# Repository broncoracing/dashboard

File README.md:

# template
Use this repo as the base for new repos.
Follow directory structure below:

```bash
├── firmware
│   └── firmware project
└── pcb
    ├── PCB layout
    ├── schematic
    └── etc
```

Upon pushing a commit, a Github action will automatically run electrical & design rule checks to verify the pcb design, then generate gerber/drill/BOM files and renderings/PDFs of the pcb and schematics.

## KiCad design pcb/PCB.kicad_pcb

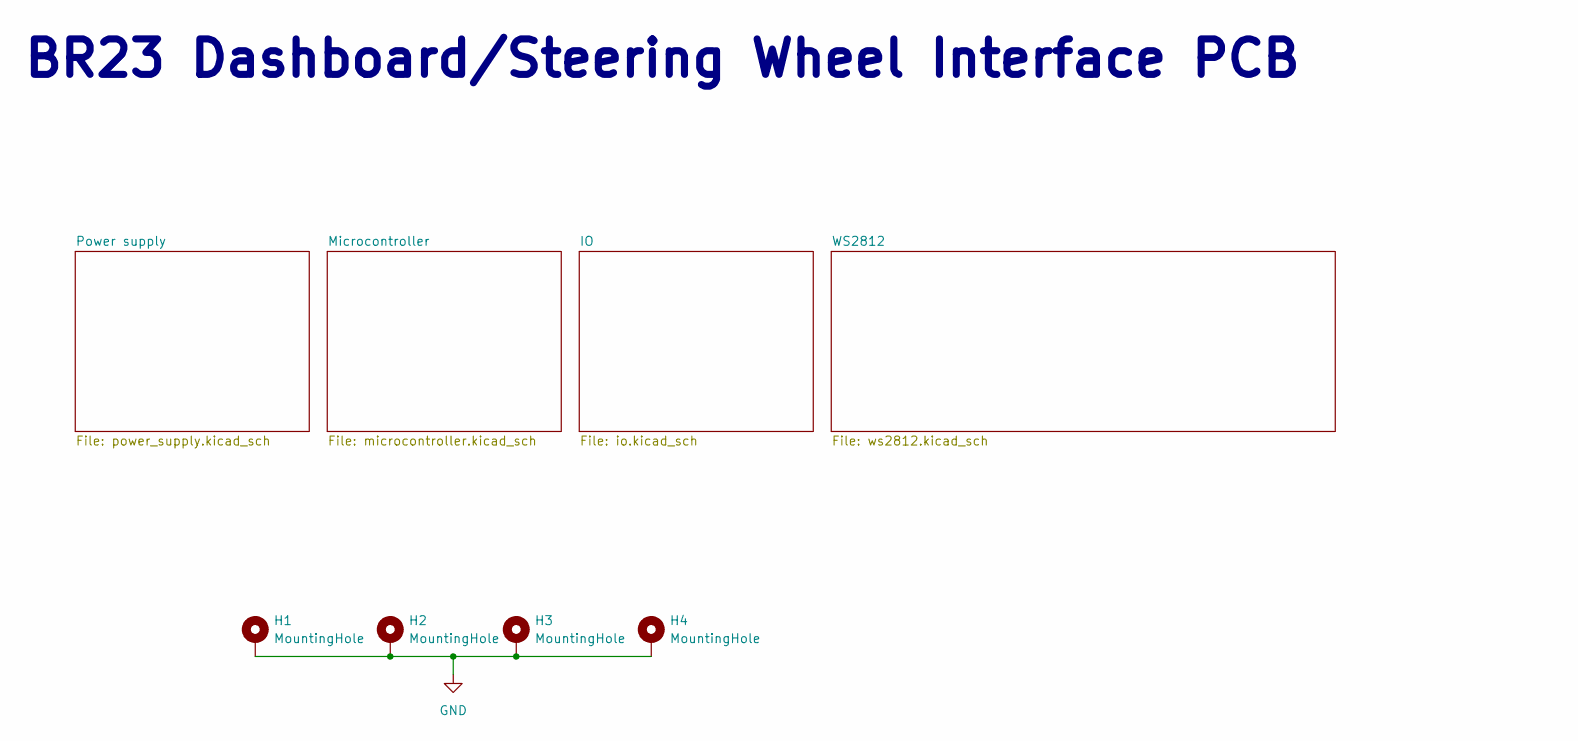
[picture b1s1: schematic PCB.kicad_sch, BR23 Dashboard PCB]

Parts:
H1, H2, H3, H4: MountingHole; MountingHole_3.5mm_Pad

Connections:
GND: H1.1, H2.1, H3.1, H4.1; also elsewhere on the board

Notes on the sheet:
BR23 Dashboard/Steering Wheel Interface PCB

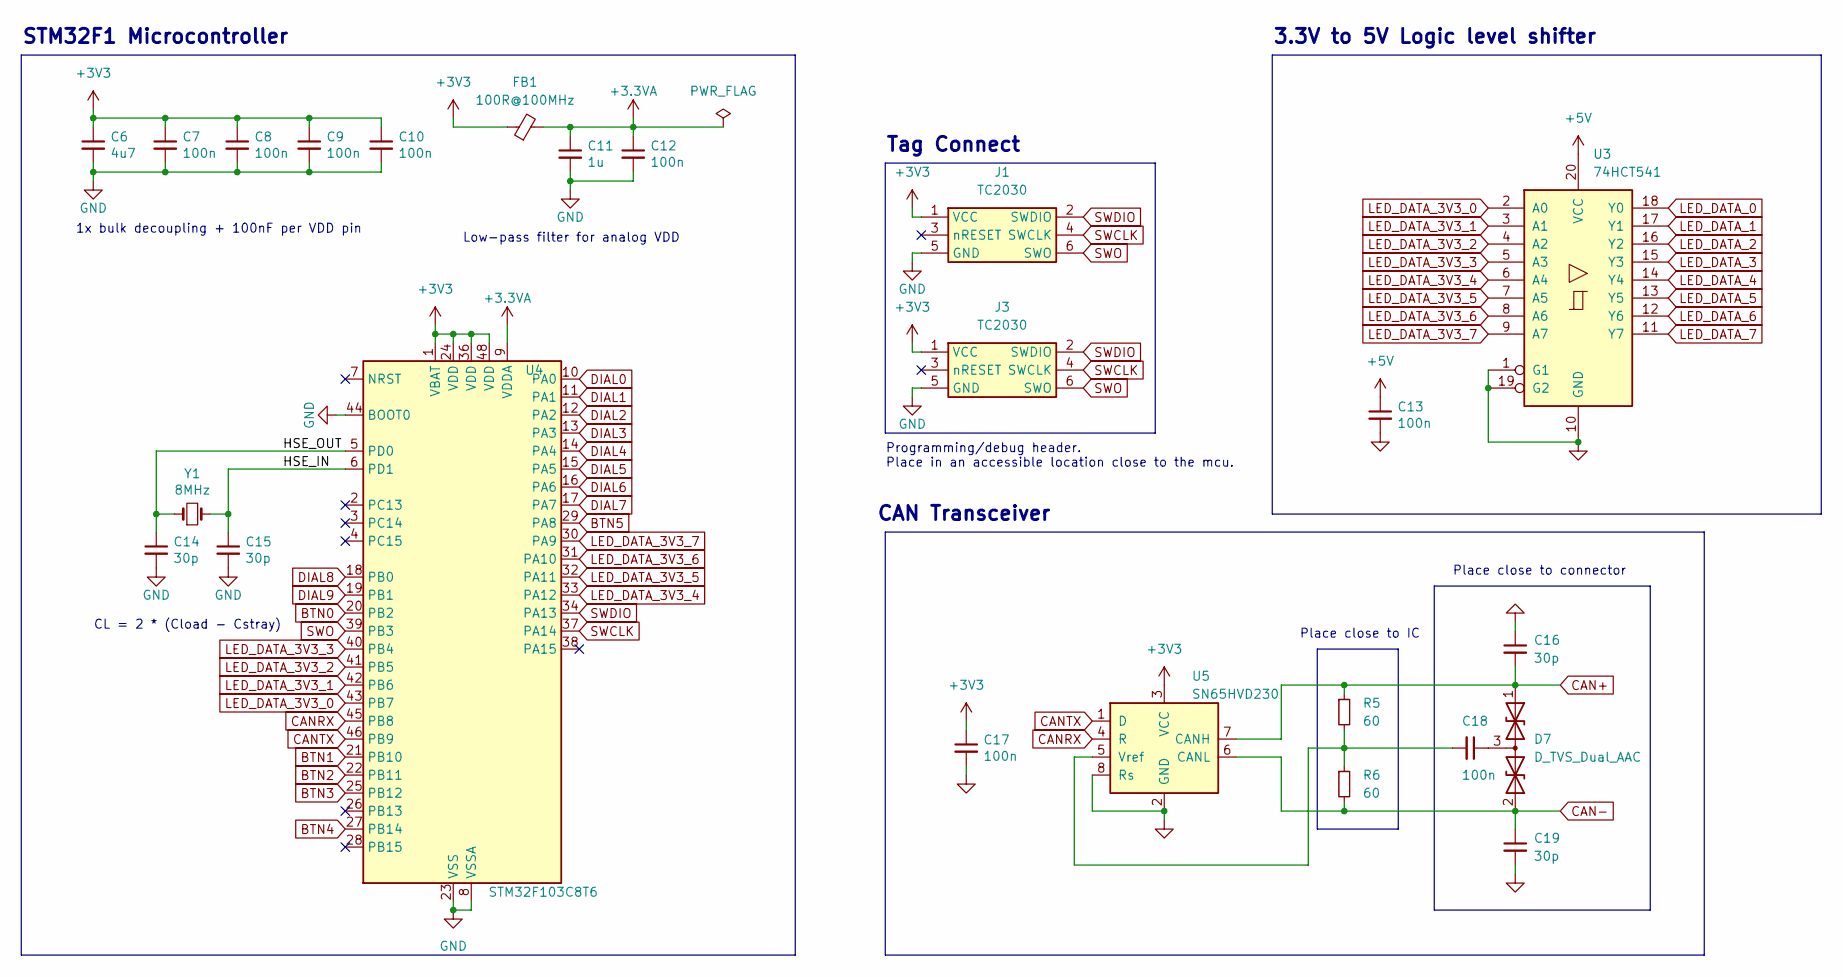
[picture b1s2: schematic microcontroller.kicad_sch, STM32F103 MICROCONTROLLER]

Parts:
C6: 4u7; C_0603_1608Metric; LCSC C19666
C7, C8, C9, C10, C12, C13, C17, C18: 100n; C_0402_1005Metric; LCSC C307331
C11: 1u; C_0603_1608Metric; LCSC C15849
C14, C15, C16, C19: 30p; C_0402_1005Metric; LCSC C1570
D7: D_TVS_Dual_AAC; SOT-323_SC-70; LCSC C151237
FB1: 100R@100MHz; R_0805_2012Metric; LCSC C1015
J1, J3: TC2030; Tag-Connect_TC2030-IDC-NL_2x03_P1.27mm_Vertical
R5, R6: 60; R_0805_2012Metric; LCSC C844855
U3: 74HCT541; SSOP-20_4.4x6.5mm_P0.65mm; LCSC C6758
U4: STM32F103C8T6; LQFP-48_7x7mm_P0.5mm; LCSC C77994
U5: SN65HVD230; SOIC-8_3.9x4.9mm_P1.27mm; LCSC C12084
Y1: 8MHz; Crystal_SMD_5032-2Pin_5.0x3.2mm; LCSC C115962

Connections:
+3.3VA: C11.1, C12.1, FB1.2, U4.9 (VDDA); also elsewhere on the board
+3V3: C6.1, C7.1, C8.1, C9.1, C10.1, C17.1, FB1.1, J1.1 (VCC), J3.1 (VCC), U4.1 (VBAT), U4.24 (VDD), U4.36 (VDD), U4.48 (VDD), U5.3 (VCC); also elsewhere on the board
+5V: C13.1, U3.20 (VCC); also elsewhere on the board
/Microcontroller/HSE_IN: C15.1, U4.6 (PD1), Y1.2
/Microcontroller/HSE_OUT: C14.1, U4.5 (PD0), Y1.1
BTN0: U4.20 (PB2); also elsewhere on the board
BTN1: U4.21 (PB10); also elsewhere on the board
BTN2: U4.22 (PB11); also elsewhere on the board
BTN3: U4.25 (PB12); also elsewhere on the board
BTN4: U4.27 (PB14); also elsewhere on the board
BTN5: U4.29 (PA8); also elsewhere on the board
CAN+: C16.2, D7.1 (A1), R5.1, U5.7 (CANH); also elsewhere on the board
CAN-: C19.1, D7.2 (A2), R6.2, U5.6 (CANL); also elsewhere on the board
CANRX: U4.45 (PB8), U5.4 (R)
CANTX: U4.46 (PB9), U5.1 (D)
DIAL0: U4.10 (PA0); also elsewhere on the board
DIAL1: U4.11 (PA1); also elsewhere on the board
DIAL2: U4.12 (PA2); also elsewhere on the board
DIAL3: U4.13 (PA3); also elsewhere on the board
DIAL4: U4.14 (PA4); also elsewhere on the board
DIAL5: U4.15 (PA5); also elsewhere on the board
DIAL6: U4.16 (PA6); also elsewhere on the board
DIAL7: U4.17 (PA7); also elsewhere on the board
DIAL8: U4.18 (PB0); also elsewhere on the board
DIAL9: U4.19 (PB1); also elsewhere on the board
GND: C6.2, C7.2, C8.2, C9.2, C10.2, C11.2, C12.2, C13.2, C14.2, C15.2, C16.1, C17.2, C19.2, J1.5 (GND), J3.5 (GND), U3.1 (G1), U3.10 (GND), U3.19 (G2), U4.8 (VSSA), U4.23 (VSS), U4.35 (VSS), U4.44 (BOOT0), U4.47 (VSS), U5.2 (GND), U5.8 (Rs); also elsewhere on the board
LED_DATA_0: U3.18 (Y0); also elsewhere on the board
LED_DATA_1: U3.17 (Y1); also elsewhere on the board
LED_DATA_2: U3.16 (Y2); also elsewhere on the board
LED_DATA_3: U3.15 (Y3); also elsewhere on the board
LED_DATA_3V3_0: U3.2 (A0), U4.43 (PB7)
LED_DATA_3V3_1: U3.3 (A1), U4.42 (PB6)
LED_DATA_3V3_2: U3.4 (A2), U4.41 (PB5)
LED_DATA_3V3_3: U3.5 (A3), U4.40 (PB4)
LED_DATA_3V3_4: U3.6 (A4), U4.33 (PA12)
LED_DATA_3V3_5: U3.7 (A5), U4.32 (PA11)
LED_DATA_3V3_6: U3.8 (A6), U4.31 (PA10)
LED_DATA_3V3_7: U3.9 (A7), U4.30 (PA9)
LED_DATA_4: U3.14 (Y4); also elsewhere on the board
LED_DATA_5: U3.13 (Y5); also elsewhere on the board
LED_DATA_6: U3.12 (Y6); also elsewhere on the board
LED_DATA_7: U3.11 (Y7); also elsewhere on the board
unnamed: C18.1, D7.3 (common)
unnamed: C18.2, R5.2, R6.1, U5.5 (Vref)
SWCLK: J1.4 (SWCLK), J3.4 (SWCLK), U4.37 (PA14)
SWDIO: J1.2 (SWDIO), J3.2 (SWDIO), U4.34 (PA13)
SWO: J1.6 (SWO), J3.6 (SWO), U4.39 (PB3)

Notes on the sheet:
3.3V to 5V Logic level shifter
Tag Connect
Low-pass filter for analog VDD
Programming/debug header. Place in an accessible location close to the mcu.
CAN Transceiver
Place close to connector
1x bulk decoupling + 100nF per VDD pin
STM32F1 Microcontroller
Place close to IC
CL = 2 * (Cload - Cstray)

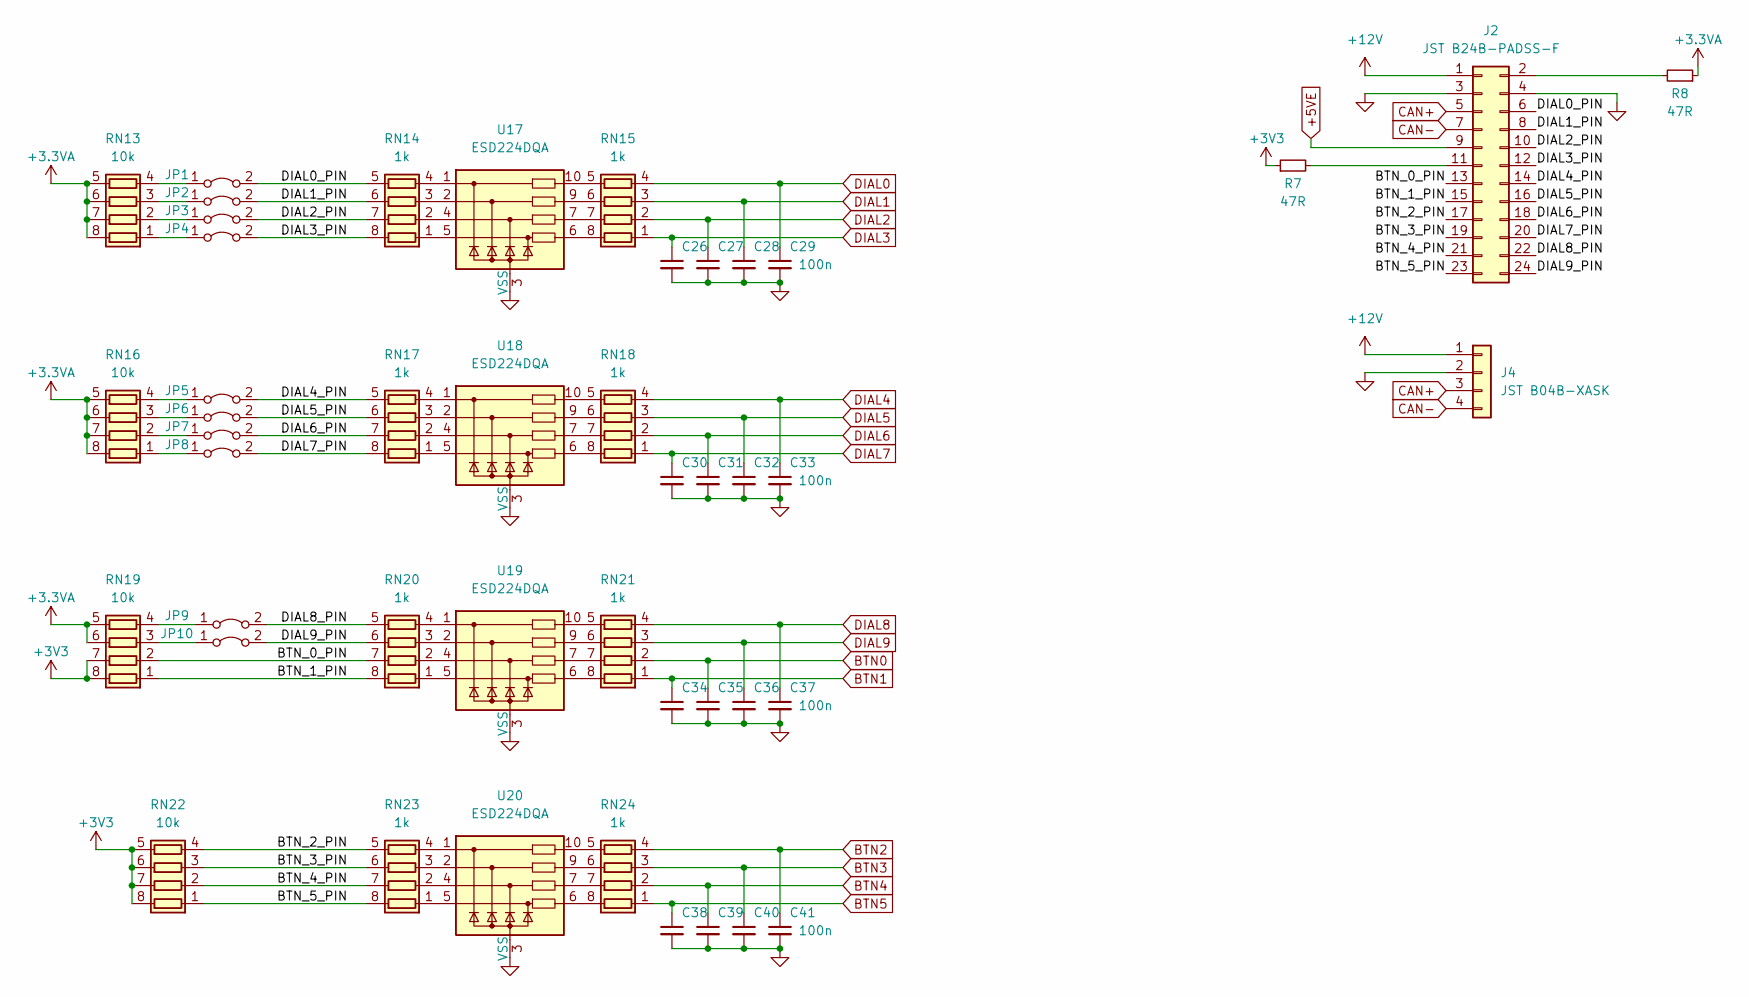
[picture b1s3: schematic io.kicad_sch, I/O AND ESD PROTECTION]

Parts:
C26, C27, C28, C29, C30, C31, C32, C33, C34, C35, C36, C37, C38, C39, C40, C41: 100n; C_0402_1005Metric; LCSC C307331
J2: JST B24B-PADSS-F; JST_B24B_PADSS; LCSC C5329907
J4: JST B04B-XASK; JST_XA_B04B-XASK-1_1x04_P2.50mm_Vertical; LCSC C160300
JP1, JP2, JP3, JP4, JP5, JP6, JP7, JP8, JP9, JP10: Jumper_2_Bridged; TestPoint_2Pads_Pitch2.54mm_Drill0.8mm
R7, R8: 47R; R_0805_2012Metric; LCSC C17714
RN13, RN16, RN19, RN22: 10k; R_Array_Convex_4x0603; LCSC C29718
RN14, RN15, RN17, RN18, RN20, RN21, RN23, RN24: 1k; R_Array_Convex_4x0603; LCSC C20197
U17, U18, U19, U20: ESD224DQA; Diodes_UDFN-10_1.0x2.5mm_P0.5mm; LCSC C1981316

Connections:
+3.3VA: R8.1, RN13.5 (R4.2), RN13.6 (R3.2), RN13.7 (R2.2), RN13.8 (R1.2), RN16.5 (R4.2), RN16.6 (R3.2), RN16.7 (R2.2), RN16.8 (R1.2), RN19.5 (R4.2), RN19.6 (R3.2); also elsewhere on the board
+3V3: R7.1, RN19.7 (R2.2), RN19.8 (R1.2), RN22.5 (R4.2), RN22.6 (R3.2), RN22.7 (R2.2), RN22.8 (R1.2); also elsewhere on the board
+5VE: J2.9; also elsewhere on the board
+12V: J2.1, J4.1; also elsewhere on the board
/IO/BTN_0_PIN: J2.13, RN19.2 (R2.1), RN20.7 (R2.2)
/IO/BTN_1_PIN: J2.15, RN19.1 (R1.1), RN20.8 (R1.2)
/IO/BTN_2_PIN: J2.17, RN22.4 (R4.1), RN23.5 (R4.2)
/IO/BTN_3_PIN: J2.19, RN22.3 (R3.1), RN23.6 (R3.2)
/IO/BTN_4_PIN: J2.21, RN22.2 (R2.1), RN23.7 (R2.2)
/IO/BTN_5_PIN: J2.23, RN22.1 (R1.1), RN23.8 (R1.2)
/IO/DIAL0_PIN: J2.6, JP1.2 (B), RN14.5 (R4.2)
/IO/DIAL1_PIN: J2.8, JP2.2 (B), RN14.6 (R3.2)
/IO/DIAL2_PIN: J2.10, JP3.2 (B), RN14.7 (R2.2)
/IO/DIAL3_PIN: J2.12, JP4.2 (B), RN14.8 (R1.2)
/IO/DIAL4_PIN: J2.14, JP5.2 (B), RN17.5 (R4.2)
/IO/DIAL5_PIN: J2.16, JP6.2 (B), RN17.6 (R3.2)
/IO/DIAL6_PIN: J2.18, JP7.2 (B), RN17.7 (R2.2)
/IO/DIAL7_PIN: J2.20, JP8.2 (B), RN17.8 (R1.2)
/IO/DIAL8_PIN: J2.22, JP9.2 (B), RN20.5 (R4.2)
/IO/DIAL9_PIN: J2.24, JP10.2 (B), RN20.6 (R3.2)
BTN0: C35.1, RN21.2 (R2.1); also elsewhere on the board
BTN1: C34.1, RN21.1 (R1.1); also elsewhere on the board
BTN2: C41.1, RN24.4 (R4.1); also elsewhere on the board
BTN3: C40.1, RN24.3 (R3.1); also elsewhere on the board
BTN4: C39.1, RN24.2 (R2.1); also elsewhere on the board
BTN5: C38.1, RN24.1 (R1.1); also elsewhere on the board
CAN+: J2.5, J4.3; also elsewhere on the board
CAN-: J2.7, J4.4; also elsewhere on the board
DIAL0: C29.1, RN15.4 (R4.1); also elsewhere on the board
DIAL1: C28.1, RN15.3 (R3.1); also elsewhere on the board
DIAL2: C27.1, RN15.2 (R2.1); also elsewhere on the board
DIAL3: C26.1, RN15.1 (R1.1); also elsewhere on the board
DIAL4: C33.1, RN18.4 (R4.1); also elsewhere on the board
DIAL5: C32.1, RN18.3 (R3.1); also elsewhere on the board
DIAL6: C31.1, RN18.2 (R2.1); also elsewhere on the board
DIAL7: C30.1, RN18.1 (R1.1); also elsewhere on the board
DIAL8: C37.1, RN21.4 (R4.1); also elsewhere on the board
DIAL9: C36.1, RN21.3 (R3.1); also elsewhere on the board
GND: C26.2, C27.2, C28.2, C29.2, C30.2, C31.2, C32.2, C33.2, C34.2, C35.2, C36.2, C37.2, C38.2, C39.2, C40.2, C41.2, J2.3, J2.4, J4.2, U17.3 (VSS), U17.8 (VSS), U18.3 (VSS), U18.8 (VSS), U19.3 (VSS), U19.8 (VSS), U20.3 (VSS), U20.8 (VSS); also elsewhere on the board
unnamed: J2.2, R8.2
unnamed: J2.11, R7.2
unnamed: JP1.1 (A), RN13.4 (R4.1)
unnamed: JP2.1 (A), RN13.3 (R3.1)
unnamed: JP3.1 (A), RN13.2 (R2.1)
unnamed: JP4.1 (A), RN13.1 (R1.1)
unnamed: JP5.1 (A), RN16.4 (R4.1)
unnamed: JP6.1 (A), RN16.3 (R3.1)
unnamed: JP7.1 (A), RN16.2 (R2.1)
unnamed: JP8.1 (A), RN16.1 (R1.1)
unnamed: JP9.1 (A), RN19.4 (R4.1)
unnamed: JP10.1 (A), RN19.3 (R3.1)
unnamed: RN14.1 (R1.1), U17.5
unnamed: RN14.2 (R2.1), U17.4
unnamed: RN14.3 (R3.1), U17.2
unnamed: RN14.4 (R4.1), U17.1
unnamed: RN15.8 (R1.2), U17.6
unnamed: RN15.7 (R2.2), U17.7
unnamed: RN15.6 (R3.2), U17.9
unnamed: RN15.5 (R4.2), U17.10
unnamed: RN17.1 (R1.1), U18.5
unnamed: RN17.2 (R2.1), U18.4
unnamed: RN17.3 (R3.1), U18.2
unnamed: RN17.4 (R4.1), U18.1
unnamed: RN18.8 (R1.2), U18.6
unnamed: RN18.7 (R2.2), U18.7
unnamed: RN18.6 (R3.2), U18.9
unnamed: RN18.5 (R4.2), U18.10
unnamed: RN20.1 (R1.1), U19.5
unnamed: RN20.2 (R2.1), U19.4
unnamed: RN20.3 (R3.1), U19.2
unnamed: RN20.4 (R4.1), U19.1
unnamed: RN21.8 (R1.2), U19.6
unnamed: RN21.7 (R2.2), U19.7
unnamed: RN21.6 (R3.2), U19.9
unnamed: RN21.5 (R4.2), U19.10
unnamed: RN23.1 (R1.1), U20.5
unnamed: RN23.2 (R2.1), U20.4
unnamed: RN23.3 (R3.1), U20.2
unnamed: RN23.4 (R4.1), U20.1
unnamed: RN24.8 (R1.2), U20.6
unnamed: RN24.7 (R2.2), U20.7
unnamed: RN24.6 (R3.2), U20.9
unnamed: RN24.5 (R4.2), U20.10

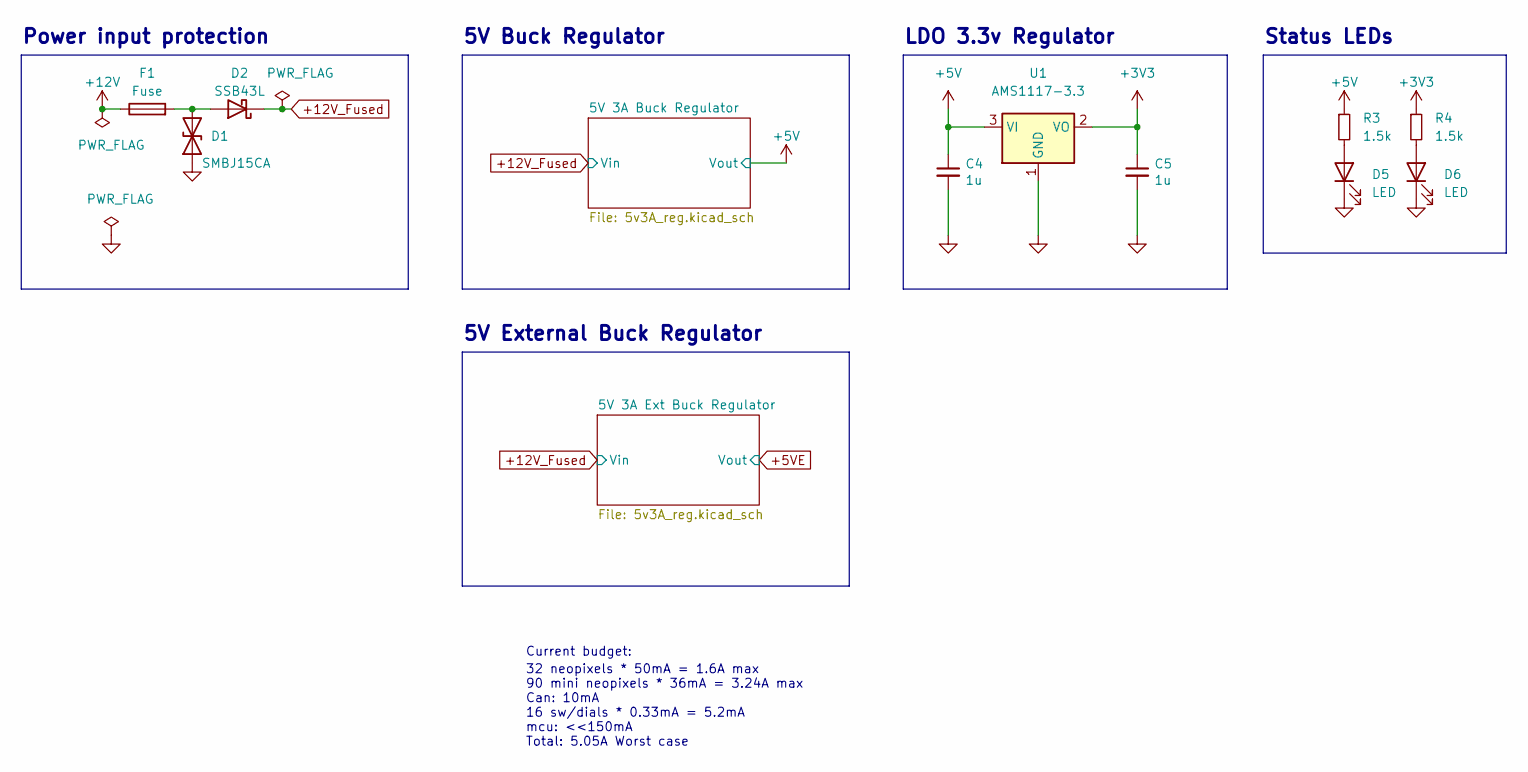
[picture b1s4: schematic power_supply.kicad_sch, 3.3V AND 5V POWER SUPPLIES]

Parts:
C4, C5: 1u; C_0603_1608Metric; LCSC C15849
D1: SMBJ15CA; D_SMB; LCSC C78809
D2: SSB43L; D_SMB; LCSC C222519
D5, D6: LED; LED_0603_1608Metric; LCSC C5875739
F1: Fuse; Fuse_0603_1608Metric; LCSC C122964
R3, R4: 1.5k; R_0603_1608Metric; LCSC C4177
U1: AMS1117-3.3; SOT-223-3_TabPin2; LCSC C6186

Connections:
+3V3: C5.1, R4.1, U1.2 (VO); also elsewhere on the board
+5V: C4.1, R3.1, U1.3 (VI); also elsewhere on the board
+12V: F1.1; also elsewhere on the board
+12V_Fused: D2.1 (K); also elsewhere on the board
GND: C4.2, C5.2, D1.1 (A1), D5.1 (K), D6.1 (K), U1.1 (GND); also elsewhere on the board
unnamed: D1.2 (A2), D2.2 (A), F1.2
unnamed: D5.2 (A), R3.2
unnamed: D6.2 (A), R4.2

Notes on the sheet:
5V External Buck Regulator
Power input protection
5V Buck Regulator
Current budget:
Status LEDs
LDO 3.3v Regulator
32 neopixels * 50mA = 1.6A max 90 mini neopixels * 36mA = 3.24A max Can: 10mA 16 sw/dials * 0.33mA = 5.2mA mcu: <<150mA Total: 5.05A Worst case

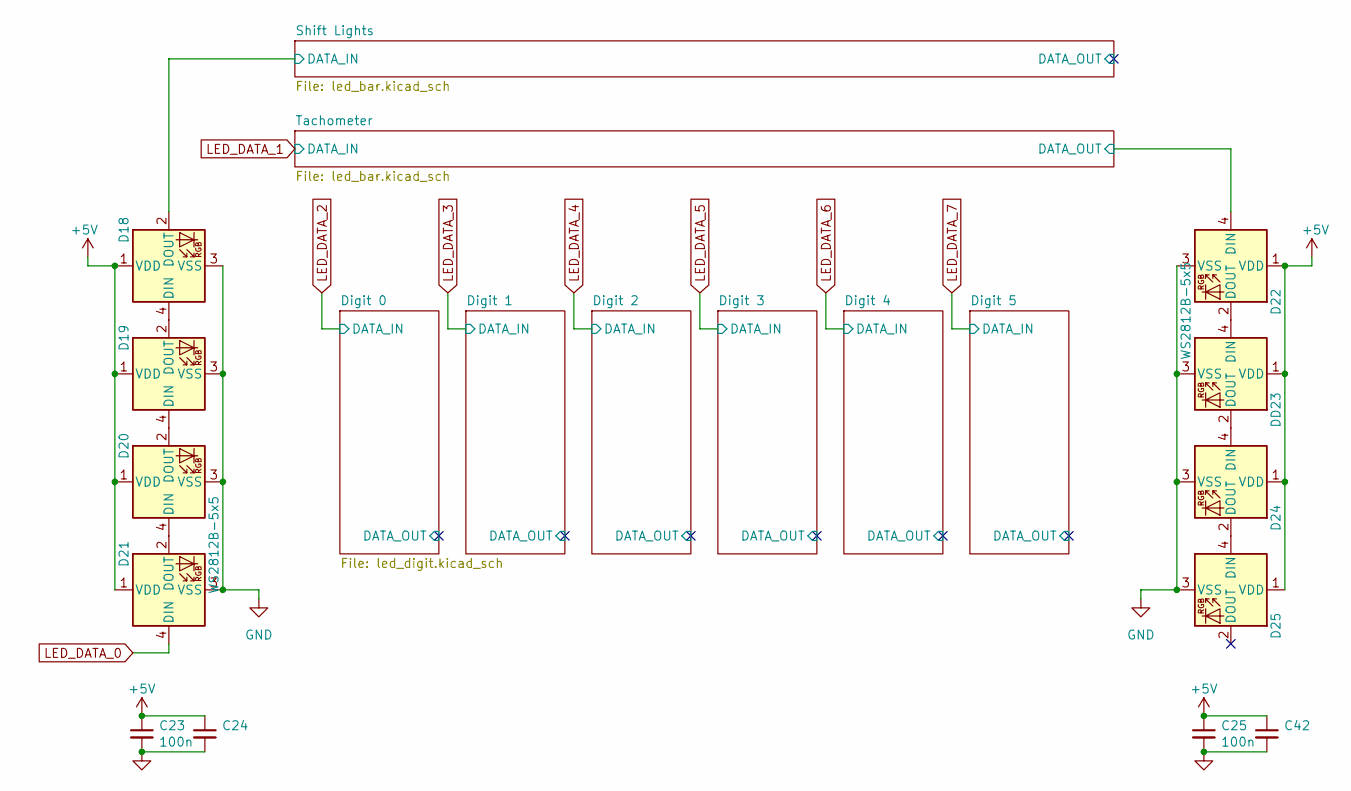
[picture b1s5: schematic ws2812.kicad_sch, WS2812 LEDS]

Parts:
C23, C24, C25, C42: 100n; C_0402_1005Metric; LCSC C307331
D18, D19, D20, D21, D22, D24, D25: WS2812B-5x5; LED_WS2812B_PLCC4_5.0x5.0mm_P3.2mm; LCSC C22371521
DD23: WS2812B-5x5; LED_WS2812B_PLCC4_5.0x5.0mm_P3.2mm; LCSC C22371521

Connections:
+5V: C23.1, C24.1, C25.1, C42.1, D18.1 (VDD), D19.1 (VDD), D20.1 (VDD), D21.1 (VDD), D22.1 (VDD), D24.1 (VDD), D25.1 (VDD), DD23.1 (VDD); also elsewhere on the board
/WS2812/Shift Lights/DATA_IN: D18.2 (DOUT); also elsewhere on the board
/WS2812/Tachometer/DATA_OUT: D22.4 (DIN); also elsewhere on the board
GND: C23.2, C24.2, C25.2, C42.2, D18.3 (VSS), D19.3 (VSS), D20.3 (VSS), D21.3 (VSS), D22.3 (VSS), D24.3 (VSS), D25.3 (VSS), DD23.3 (VSS); also elsewhere on the board
LED_DATA_0: D21.4 (DIN); also elsewhere on the board
unnamed: D18.4 (DIN), D19.2 (DOUT)
unnamed: D19.4 (DIN), D20.2 (DOUT)
unnamed: D20.4 (DIN), D21.2 (DOUT)
unnamed: D22.2 (DOUT), DD23.4 (DIN)
unnamed: D24.4 (DIN), DD23.2 (DOUT)
unnamed: D24.2 (DOUT), D25.4 (DIN)

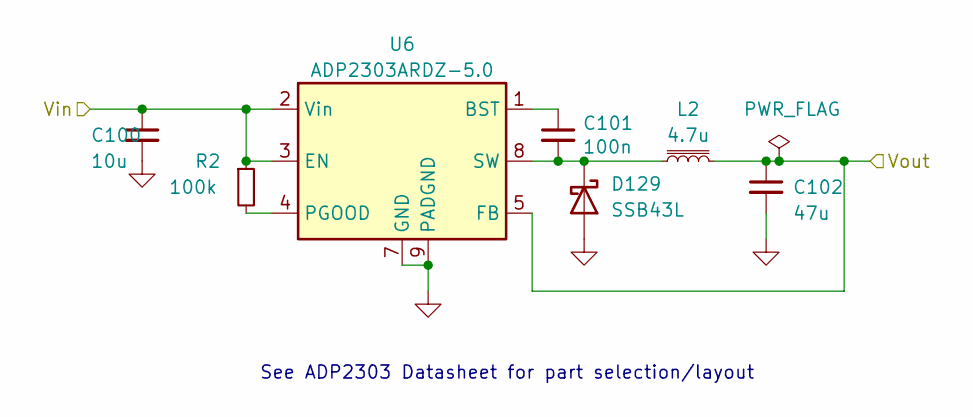
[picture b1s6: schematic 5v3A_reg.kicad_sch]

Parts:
C100: 10u; C_0805_2012Metric; LCSC C440198
C101: 100n; C_0402_1005Metric; LCSC C307331
C102: 47u; C_0805_2012Metric; LCSC C16780
D129: SSB43L; D_SMB; LCSC C222519
L2: 4.7u; L_7.3x7.3_H3.5; LCSC C497878
R2: 100k; R_0402_1005Metric; LCSC C25086
U6: ADP2303ARDZ-5.0; SOIC-8-1EP_3.9x4.9mm_P1.27mm_EP2.29x3mm; LCSC C659153

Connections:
+5VE: C102.1, L2.2, U6.5 (FB); also elsewhere on the board
+12V_Fused: C100.1, R2.1, U6.2 (Vin), U6.3 (EN); also elsewhere on the board
GND: C100.2, C102.2, D129.2 (A), U6.7 (GND), U6.9 (PADGND); also elsewhere on the board
unnamed: C101.2, D129.1 (K), L2.1, U6.8 (SW)
unnamed: C101.1, U6.1 (BST)
unnamed: R2.2, U6.4 (PGOOD)

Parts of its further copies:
C97: 10u; C_0805_2012Metric; LCSC C440198
C98: 100n; C_0402_1005Metric; LCSC C307331
C99: 47u; C_0805_2012Metric; LCSC C16780
D128: SSB43L; D_SMB; LCSC C222519
L1: 4.7u; L_7.3x7.3_H3.5; LCSC C497878
R1: 100k; R_0402_1005Metric; LCSC C25086
U2: ADP2303ARDZ-5.0; SOIC-8-1EP_3.9x4.9mm_P1.27mm_EP2.29x3mm; LCSC C659153

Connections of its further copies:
+5V: C99.1, L1.2, U2.5 (FB); also elsewhere on the board
+12V_Fused: C97.1, R1.1, U2.2 (Vin), U2.3 (EN); also elsewhere on the board
GND: C97.2, C99.2, D128.2 (A), U2.7 (GND), U2.9 (PADGND); also elsewhere on the board
unnamed: C98.2, D128.1 (K), L1.1, U2.8 (SW)
unnamed: C98.1, U2.1 (BST)
unnamed: R1.2, U2.4 (PGOOD)

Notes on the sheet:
See ADP2303 Datasheet for part selection/layout

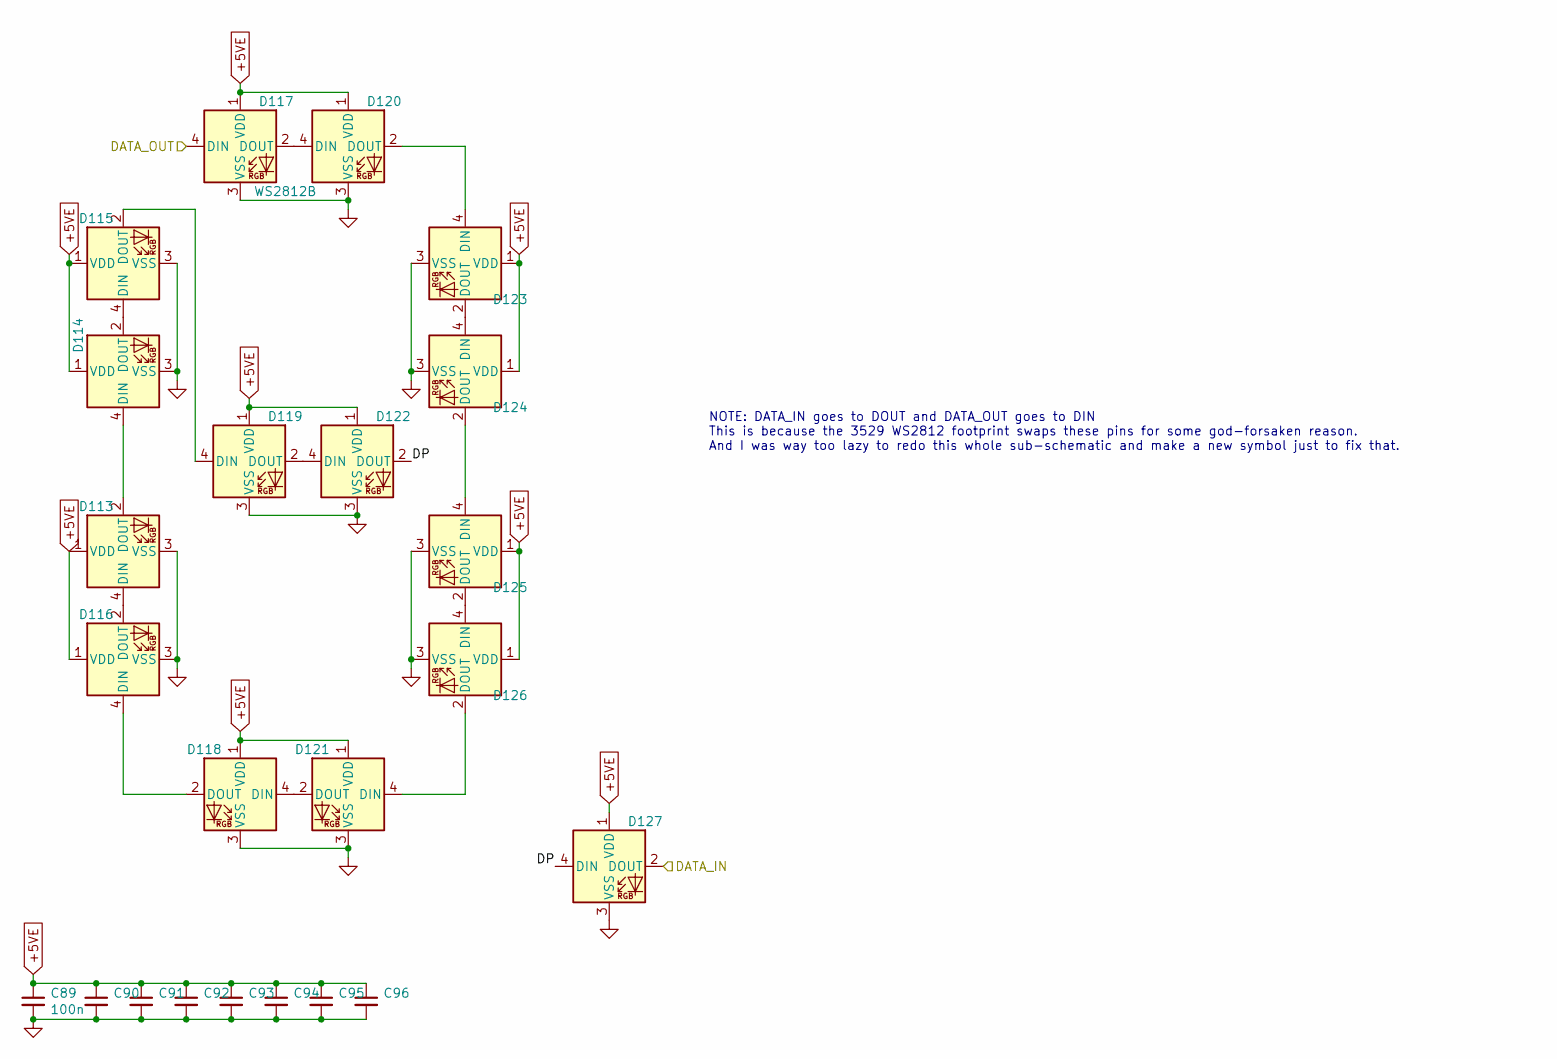
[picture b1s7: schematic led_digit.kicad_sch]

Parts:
C89, C90, C91, C92, C93, C94, C95, C96: 100n; C_0402_1005Metric; LCSC C307331
D113, D114, D115, D116, D117, D118, D119, D120, D121, D122, D123, D124, D125, D126, D127: WS2812B; LED_Kingbright_AAA3528ESGCT; LCSC C22371521

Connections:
+5VE: C89.1, C90.1, C91.1, C92.1, C93.1, C94.1, C95.1, C96.1, D113.1 (VDD), D114.1 (VDD), D115.1 (VDD), D116.1 (VDD), D117.1 (VDD), D118.1 (VDD), D119.1 (VDD), D120.1 (VDD), D121.1 (VDD), D122.1 (VDD), D123.1 (VDD), D124.1 (VDD), D125.1 (VDD), D126.1 (VDD), D127.1 (VDD); also elsewhere on the board
/WS2812/Digit 5/DATA_OUT: D117.4 (DIN)
/WS2812/Digit 5/DP: D122.2 (DOUT), D127.4 (DIN)
GND: C89.2, C90.2, C91.2, C92.2, C93.2, C94.2, C95.2, C96.2, D113.3 (VSS), D114.3 (VSS), D115.3 (VSS), D116.3 (VSS), D117.3 (VSS), D118.3 (VSS), D119.3 (VSS), D120.3 (VSS), D121.3 (VSS), D122.3 (VSS), D123.3 (VSS), D124.3 (VSS), D125.3 (VSS), D126.3 (VSS), D127.3 (VSS); also elsewhere on the board
LED_DATA_7: D127.2 (DOUT); also elsewhere on the board
unnamed: D113.4 (DIN), D114.2 (DOUT)
unnamed: D113.2 (DOUT), D119.4 (DIN)
unnamed: D114.4 (DIN), D115.2 (DOUT)
unnamed: D115.4 (DIN), D116.2 (DOUT)
unnamed: D116.4 (DIN), D118.2 (DOUT)
unnamed: D117.2 (DOUT), D120.4 (DIN)
unnamed: D118.4 (DIN), D121.2 (DOUT)
unnamed: D119.2 (DOUT), D122.4 (DIN)
unnamed: D120.2 (DOUT), D123.4 (DIN)
unnamed: D121.4 (DIN), D126.2 (DOUT)
unnamed: D123.2 (DOUT), D124.4 (DIN)
unnamed: D124.2 (DOUT), D125.4 (DIN)
unnamed: D125.2 (DOUT), D126.4 (DIN)

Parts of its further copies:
C49, C50, C51, C52, C53, C54, C55, C56, C57, C58, C59, C60, C61, C62, C63, C64, C65, C66, C67, C68, C69, C70, C71, C72, C73, C74, C75, C76, C77, C78, C79, C80, C81, C82, C83, C84, C85, C86, C87, C88: 100n; C_0402_1005Metric; LCSC C307331
D38, D39, D40, D41, D42, D43, D44, D45, D46, D47, D48, D49, D50, D51, D52, D53, D54, D55, D56, D57, D58, D59, D60, D61, D62, D63, D64, D65, D66, D67, D68, D69, D70, D71, D72, D73, D74, D75, D76, D77, D78, D79, D80, D81, D82, D83, D84, D85, D86, D87, D88, D89, D90, D91, D92, D93, D94, D95, D96, D97, D98, D99, D100, D101, D102, D103, D104, D105, D106, D107, D108, D109, D110, D111, D112: WS2812B; LED_Kingbright_AAA3528ESGCT; LCSC C22371521

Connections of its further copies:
+5VE: C49.1, C50.1, C51.1, C52.1, C53.1, C54.1, C55.1, C56.1, C57.1, C58.1, C59.1, C60.1, C61.1, C62.1, C63.1, C64.1, C65.1, C66.1, C67.1, C68.1, C69.1, C70.1, C71.1, C72.1, C73.1, C74.1, C75.1, C76.1, C77.1, C78.1, C79.1, C80.1, C81.1, C82.1, C83.1, C84.1, C85.1, C86.1, C87.1, C88.1, D38.1 (VDD), D39.1 (VDD), D40.1 (VDD), D41.1 (VDD), D42.1 (VDD), D43.1 (VDD), D44.1 (VDD), D45.1 (VDD), D46.1 (VDD), D47.1 (VDD), D48.1 (VDD), D49.1 (VDD), D50.1 (VDD), D51.1 (VDD), D52.1 (VDD), D53.1 (VDD), D54.1 (VDD), D55.1 (VDD), D56.1 (VDD), D57.1 (VDD), D58.1 (VDD), D59.1 (VDD), D60.1 (VDD), D61.1 (VDD), D62.1 (VDD), D63.1 (VDD), D64.1 (VDD), D65.1 (VDD), D66.1 (VDD), D67.1 (VDD), D68.1 (VDD), D69.1 (VDD), D70.1 (VDD), D71.1 (VDD), D72.1 (VDD), D73.1 (VDD), D74.1 (VDD), D75.1 (VDD), D76.1 (VDD), D77.1 (VDD), D78.1 (VDD), D79.1 (VDD), D80.1 (VDD), D81.1 (VDD), D82.1 (VDD), D83.1 (VDD), D84.1 (VDD), D85.1 (VDD), D86.1 (VDD), D87.1 (VDD), D88.1 (VDD), D89.1 (VDD), D90.1 (VDD), D91.1 (VDD), D92.1 (VDD), D93.1 (VDD), D94.1 (VDD), D95.1 (VDD), D96.1 (VDD), D97.1 (VDD), D98.1 (VDD), D99.1 (VDD), D100.1 (VDD), D101.1 (VDD), D102.1 (VDD), D103.1 (VDD), D104.1 (VDD), D105.1 (VDD), D106.1 (VDD), D107.1 (VDD), D108.1 (VDD), D109.1 (VDD), D110.1 (VDD), D111.1 (VDD), D112.1 (VDD); also elsewhere on the board
/WS2812/Digit 0/DATA_OUT: D57.4 (DIN)
/WS2812/Digit 0/DP: D62.2 (DOUT), D67.4 (DIN)
/WS2812/Digit 1/DATA_OUT: D42.4 (DIN)
/WS2812/Digit 1/DP: D47.2 (DOUT), D52.4 (DIN)
/WS2812/Digit 2/DATA_OUT: D72.4 (DIN)
/WS2812/Digit 2/DP: D77.2 (DOUT), D82.4 (DIN)
/WS2812/Digit 3/DATA_OUT: D87.4 (DIN)
/WS2812/Digit 3/DP: D92.2 (DOUT), D97.4 (DIN)
/WS2812/Digit 4/DATA_OUT: D102.4 (DIN)
/WS2812/Digit 4/DP: D107.2 (DOUT), D112.4 (DIN)
GND: C49.2, C50.2, C51.2, C52.2, C53.2, C54.2, C55.2, C56.2, C57.2, C58.2, C59.2, C60.2, C61.2, C62.2, C63.2, C64.2, C65.2, C66.2, C67.2, C68.2, C69.2, C70.2, C71.2, C72.2, C73.2, C74.2, C75.2, C76.2, C77.2, C78.2, C79.2, C80.2, C81.2, C82.2, C83.2, C84.2, C85.2, C86.2, C87.2, C88.2, D38.3 (VSS), D39.3 (VSS), D40.3 (VSS), D41.3 (VSS), D42.3 (VSS), D43.3 (VSS), D44.3 (VSS), D45.3 (VSS), D46.3 (VSS), D47.3 (VSS), D48.3 (VSS), D49.3 (VSS), D50.3 (VSS), D51.3 (VSS), D52.3 (VSS), D53.3 (VSS), D54.3 (VSS), D55.3 (VSS), D56.3 (VSS), D57.3 (VSS), D58.3 (VSS), D59.3 (VSS), D60.3 (VSS), D61.3 (VSS), D62.3 (VSS), D63.3 (VSS), D64.3 (VSS), D65.3 (VSS), D66.3 (VSS), D67.3 (VSS), D68.3 (VSS), D69.3 (VSS), D70.3 (VSS), D71.3 (VSS), D72.3 (VSS), D73.3 (VSS), D74.3 (VSS), D75.3 (VSS), D76.3 (VSS), D77.3 (VSS), D78.3 (VSS), D79.3 (VSS), D80.3 (VSS), D81.3 (VSS), D82.3 (VSS), D83.3 (VSS), D84.3 (VSS), D85.3 (VSS), D86.3 (VSS), D87.3 (VSS), D88.3 (VSS), D89.3 (VSS), D90.3 (VSS), D91.3 (VSS), D92.3 (VSS), D93.3 (VSS), D94.3 (VSS), D95.3 (VSS), D96.3 (VSS), D97.3 (VSS), D98.3 (VSS), D99.3 (VSS), D100.3 (VSS), D101.3 (VSS), D102.3 (VSS), D103.3 (VSS), D104.3 (VSS), D105.3 (VSS), D106.3 (VSS), D107.3 (VSS), D108.3 (VSS), D109.3 (VSS), D110.3 (VSS), D111.3 (VSS), D112.3 (VSS); also elsewhere on the board
LED_DATA_2: D67.2 (DOUT); also elsewhere on the board
LED_DATA_3: D52.2 (DOUT); also elsewhere on the board
LED_DATA_4: D82.2 (DOUT); also elsewhere on the board
LED_DATA_5: D97.2 (DOUT); also elsewhere on the board
LED_DATA_6: D112.2 (DOUT); also elsewhere on the board
unnamed: D38.4 (DIN), D39.2 (DOUT)
unnamed: D38.2 (DOUT), D44.4 (DIN)
unnamed: D39.4 (DIN), D40.2 (DOUT)
unnamed: D40.4 (DIN), D41.2 (DOUT)
unnamed: D41.4 (DIN), D43.2 (DOUT)
unnamed: D42.2 (DOUT), D45.4 (DIN)
unnamed: D43.4 (DIN), D46.2 (DOUT)
unnamed: D44.2 (DOUT), D47.4 (DIN)
unnamed: D45.2 (DOUT), D48.4 (DIN)
unnamed: D46.4 (DIN), D51.2 (DOUT)
unnamed: D48.2 (DOUT), D49.4 (DIN)
unnamed: D49.2 (DOUT), D50.4 (DIN)
unnamed: D50.2 (DOUT), D51.4 (DIN)
unnamed: D53.4 (DIN), D54.2 (DOUT)
unnamed: D53.2 (DOUT), D59.4 (DIN)
unnamed: D54.4 (DIN), D55.2 (DOUT)
unnamed: D55.4 (DIN), D56.2 (DOUT)
unnamed: D56.4 (DIN), D58.2 (DOUT)
unnamed: D57.2 (DOUT), D60.4 (DIN)
unnamed: D58.4 (DIN), D61.2 (DOUT)
unnamed: D59.2 (DOUT), D62.4 (DIN)
unnamed: D60.2 (DOUT), D63.4 (DIN)
unnamed: D61.4 (DIN), D66.2 (DOUT)
unnamed: D63.2 (DOUT), D64.4 (DIN)
unnamed: D64.2 (DOUT), D65.4 (DIN)
unnamed: D65.2 (DOUT), D66.4 (DIN)
unnamed: D68.4 (DIN), D69.2 (DOUT)
unnamed: D68.2 (DOUT), D74.4 (DIN)
unnamed: D69.4 (DIN), D70.2 (DOUT)
unnamed: D70.4 (DIN), D71.2 (DOUT)
unnamed: D71.4 (DIN), D73.2 (DOUT)
unnamed: D72.2 (DOUT), D75.4 (DIN)
unnamed: D73.4 (DIN), D76.2 (DOUT)
unnamed: D74.2 (DOUT), D77.4 (DIN)
unnamed: D75.2 (DOUT), D78.4 (DIN)
unnamed: D76.4 (DIN), D81.2 (DOUT)
unnamed: D78.2 (DOUT), D79.4 (DIN)
unnamed: D79.2 (DOUT), D80.4 (DIN)
unnamed: D80.2 (DOUT), D81.4 (DIN)
unnamed: D83.4 (DIN), D84.2 (DOUT)
unnamed: D83.2 (DOUT), D89.4 (DIN)
unnamed: D84.4 (DIN), D85.2 (DOUT)
unnamed: D85.4 (DIN), D86.2 (DOUT)
unnamed: D86.4 (DIN), D88.2 (DOUT)
unnamed: D87.2 (DOUT), D90.4 (DIN)
unnamed: D88.4 (DIN), D91.2 (DOUT)
unnamed: D89.2 (DOUT), D92.4 (DIN)
unnamed: D90.2 (DOUT), D93.4 (DIN)
unnamed: D91.4 (DIN), D96.2 (DOUT)
unnamed: D93.2 (DOUT), D94.4 (DIN)
unnamed: D94.2 (DOUT), D95.4 (DIN)
unnamed: D95.2 (DOUT), D96.4 (DIN)
unnamed: D98.4 (DIN), D99.2 (DOUT)
unnamed: D100.4 (DIN), D101.2 (DOUT)
unnamed: D99.4 (DIN), D100.2 (DOUT)
unnamed: D101.4 (DIN), D103.2 (DOUT)
unnamed: D102.2 (DOUT), D105.4 (DIN)
unnamed: D103.4 (DIN), D106.2 (DOUT)
unnamed: D98.2 (DOUT), D104.4 (DIN)
unnamed: D104.2 (DOUT), D107.4 (DIN)
unnamed: D105.2 (DOUT), D108.4 (DIN)
unnamed: D106.4 (DIN), D111.2 (DOUT)
unnamed: D108.2 (DOUT), D109.4 (DIN)
unnamed: D109.2 (DOUT), D110.4 (DIN)
unnamed: D110.2 (DOUT), D111.4 (DIN)

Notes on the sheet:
NOTE: DATA_IN goes to DOUT and DATA_OUT goes to DIN This is because the 3529 WS2812 footprint swaps these pins for some god-forsaken reason. And I was way too lazy to redo this whole sub-schematic and make a new symbol just to fix that.

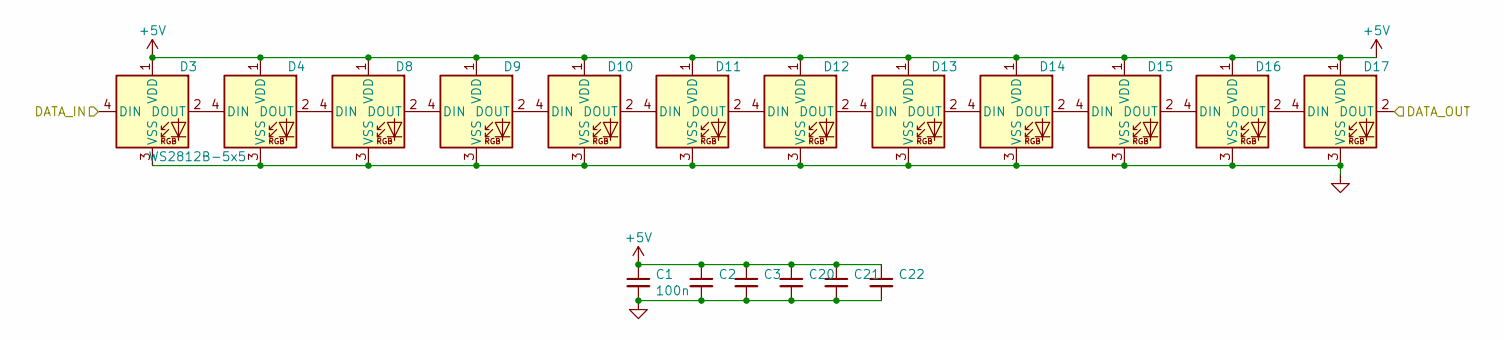
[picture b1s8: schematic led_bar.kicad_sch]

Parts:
C1, C2, C3, C20, C21, C22: 100n; C_0402_1005Metric; LCSC C307331
D3, D4, D8, D9, D10, D11, D12, D13, D14, D15, D16, D17: WS2812B-5x5; LED_WS2812B_PLCC4_5.0x5.0mm_P3.2mm; LCSC C22371521

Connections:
+5V: C1.1, C2.1, C3.1, C20.1, C21.1, C22.1, D3.1 (VDD), D4.1 (VDD), D8.1 (VDD), D9.1 (VDD), D10.1 (VDD), D11.1 (VDD), D12.1 (VDD), D13.1 (VDD), D14.1 (VDD), D15.1 (VDD), D16.1 (VDD), D17.1 (VDD); also elsewhere on the board
/WS2812/Tachometer/DATA_OUT: D17.2 (DOUT); also elsewhere on the board
GND: C1.2, C2.2, C3.2, C20.2, C21.2, C22.2, D3.3 (VSS), D4.3 (VSS), D8.3 (VSS), D9.3 (VSS), D10.3 (VSS), D11.3 (VSS), D12.3 (VSS), D13.3 (VSS), D14.3 (VSS), D15.3 (VSS), D16.3 (VSS), D17.3 (VSS); also elsewhere on the board
LED_DATA_1: D3.4 (DIN); also elsewhere on the board
unnamed: D3.2 (DOUT), D4.4 (DIN)
unnamed: D4.2 (DOUT), D8.4 (DIN)
unnamed: D8.2 (DOUT), D9.4 (DIN)
unnamed: D9.2 (DOUT), D10.4 (DIN)
unnamed: D10.2 (DOUT), D11.4 (DIN)
unnamed: D11.2 (DOUT), D12.4 (DIN)
unnamed: D12.2 (DOUT), D13.4 (DIN)
unnamed: D13.2 (DOUT), D14.4 (DIN)
unnamed: D14.2 (DOUT), D15.4 (DIN)
unnamed: D15.2 (DOUT), D16.4 (DIN)
unnamed: D16.2 (DOUT), D17.4 (DIN)

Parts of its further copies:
C43, C44, C45, C46, C47, C48: 100n; C_0402_1005Metric; LCSC C307331
D26, D27, D28, D29, D30, D31, D32, D33, D34, D35, D36, D37: WS2812B-5x5; LED_WS2812B_PLCC4_5.0x5.0mm_P3.2mm; LCSC C22371521

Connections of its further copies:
+5V: C43.1, C44.1, C45.1, C46.1, C47.1, C48.1, D26.1 (VDD), D27.1 (VDD), D28.1 (VDD), D29.1 (VDD), D30.1 (VDD), D31.1 (VDD), D32.1 (VDD), D33.1 (VDD), D34.1 (VDD), D35.1 (VDD), D36.1 (VDD), D37.1 (VDD); also elsewhere on the board
/WS2812/Shift Lights/DATA_IN: D26.4 (DIN); also elsewhere on the board
/WS2812/Shift Lights/DATA_OUT: D37.2 (DOUT)
GND: C43.2, C44.2, C45.2, C46.2, C47.2, C48.2, D26.3 (VSS), D27.3 (VSS), D28.3 (VSS), D29.3 (VSS), D30.3 (VSS), D31.3 (VSS), D32.3 (VSS), D33.3 (VSS), D34.3 (VSS), D35.3 (VSS), D36.3 (VSS), D37.3 (VSS); also elsewhere on the board
unnamed: D26.2 (DOUT), D27.4 (DIN)
unnamed: D27.2 (DOUT), D28.4 (DIN)
unnamed: D28.2 (DOUT), D29.4 (DIN)
unnamed: D29.2 (DOUT), D30.4 (DIN)
unnamed: D30.2 (DOUT), D31.4 (DIN)
unnamed: D31.2 (DOUT), D32.4 (DIN)
unnamed: D32.2 (DOUT), D33.4 (DIN)
unnamed: D33.2 (DOUT), D34.4 (DIN)
unnamed: D34.2 (DOUT), D35.4 (DIN)
unnamed: D35.2 (DOUT), D36.4 (DIN)
unnamed: D36.2 (DOUT), D37.4 (DIN)
